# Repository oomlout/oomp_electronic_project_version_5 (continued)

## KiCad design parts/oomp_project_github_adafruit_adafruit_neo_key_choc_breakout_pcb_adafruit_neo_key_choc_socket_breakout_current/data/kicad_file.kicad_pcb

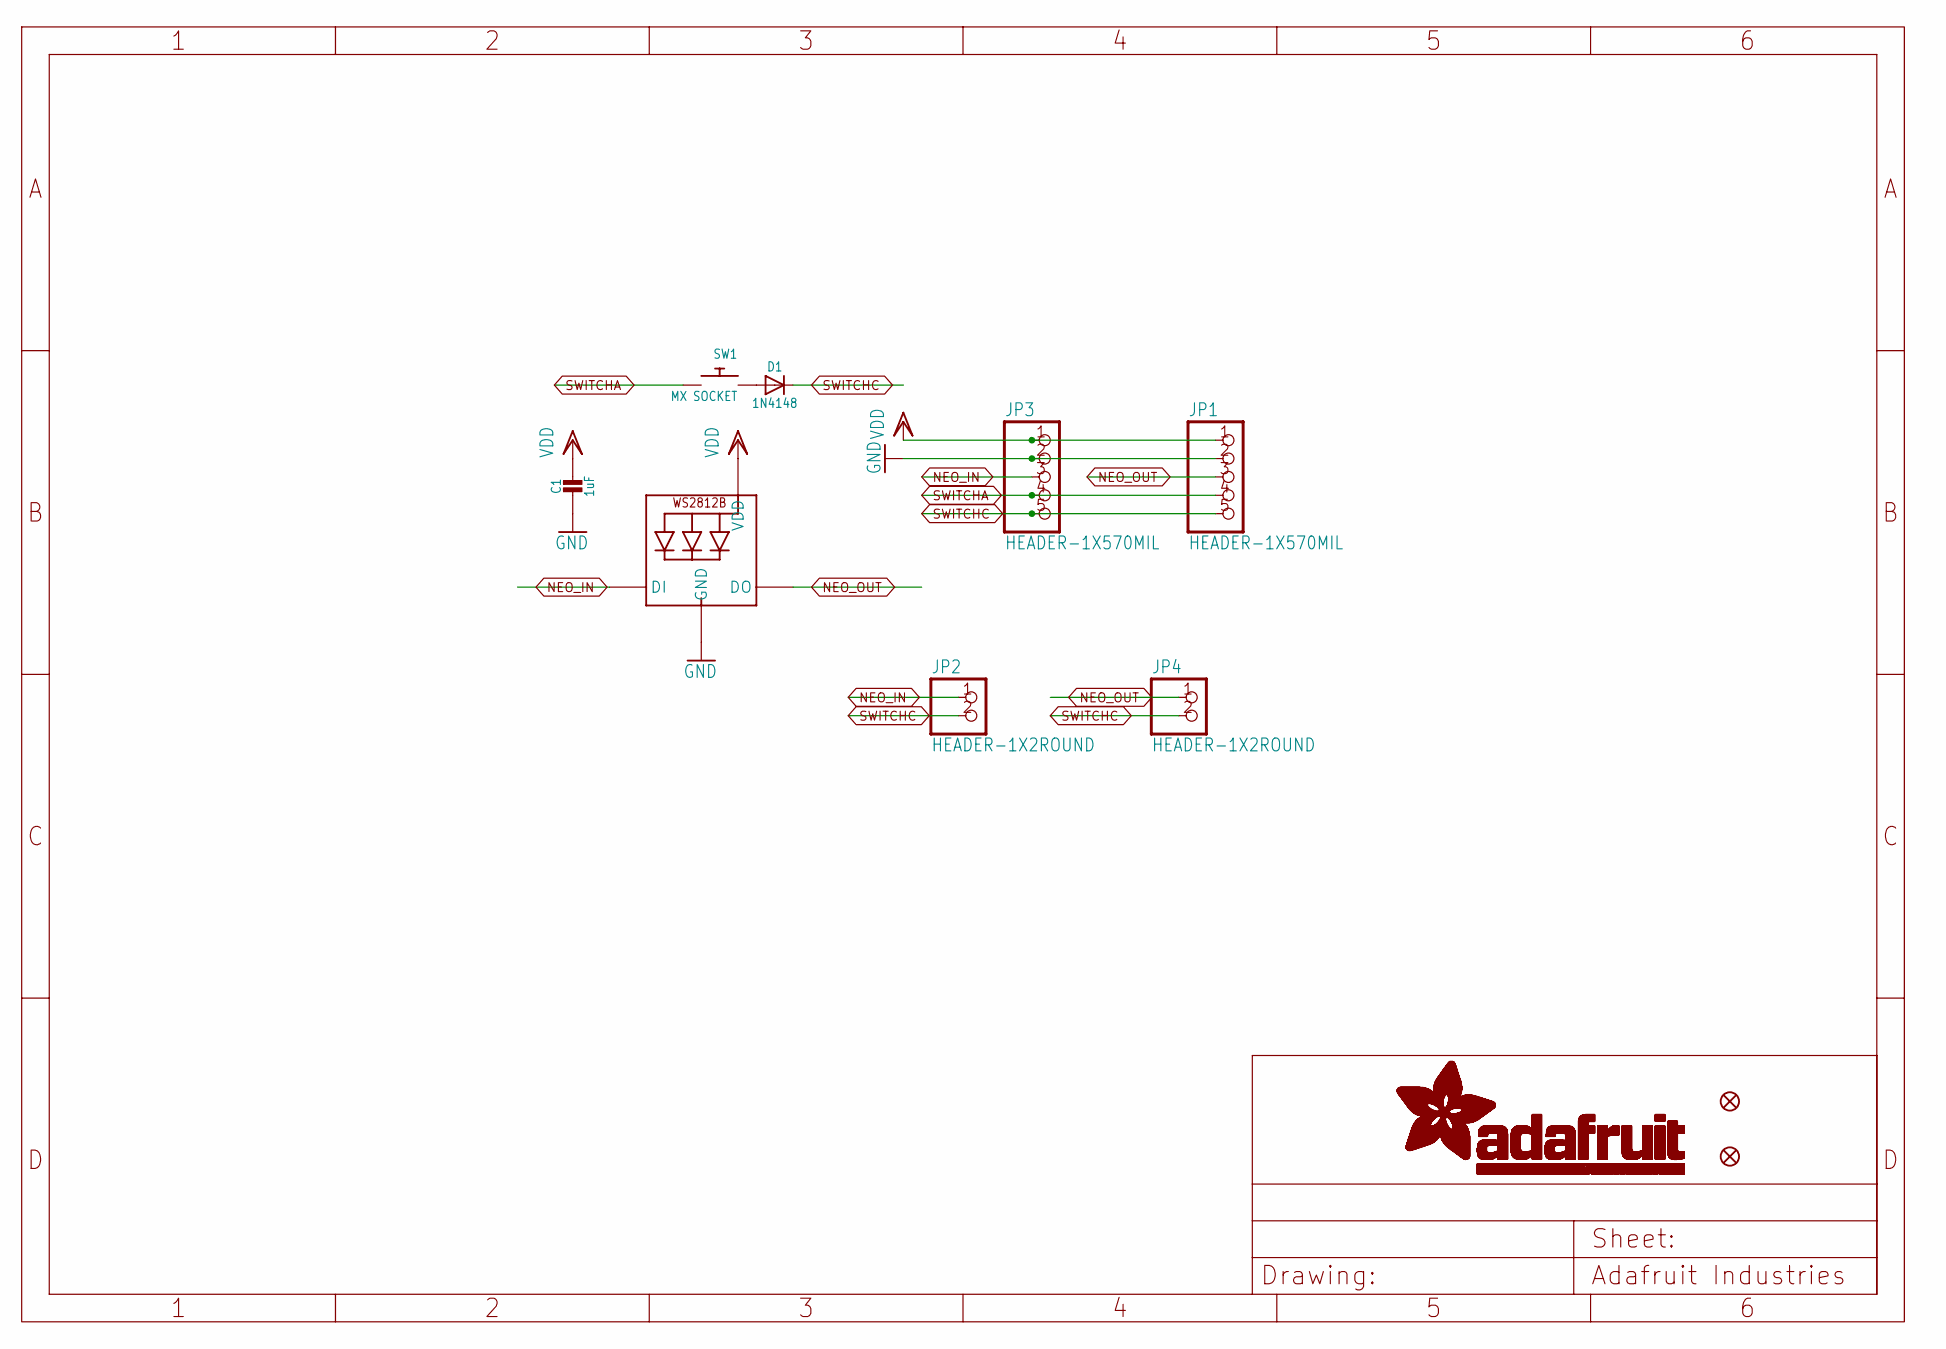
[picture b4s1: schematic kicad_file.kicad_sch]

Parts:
C1: 1uF; 0603-NO
D1: 1N4148; SOD-323
FID3, FID4: FIDUCIAL_1MM
JP1, JP3: HEADER-1X570MIL; 1X05_ROUND_70
JP2, JP4: HEADER-1X2ROUND; 1X02_ROUND
LED1: WS2812B_SK6812E; NEO3535_REVERSE
SW1: MX SOCKET; KAILH_CHOC_SOCKET

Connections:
GND: C1.2, JP1.2, JP3.2, LED1.3-GND (GND)
unnamed: D1.A, SW1.1
NEO_IN: JP2.1, JP3.3, LED1.4-DIN (DI)
NEO_OUT: JP1.3, JP4.1, LED1.2-DOUT (DO)
SWITCHA: JP1.4, JP3.4, SW1.2
SWITCHC: D1.C, JP1.5, JP2.2, JP3.5, JP4.2
VDD: C1.1, JP1.1, JP3.1, LED1.1-VDD (VDD)

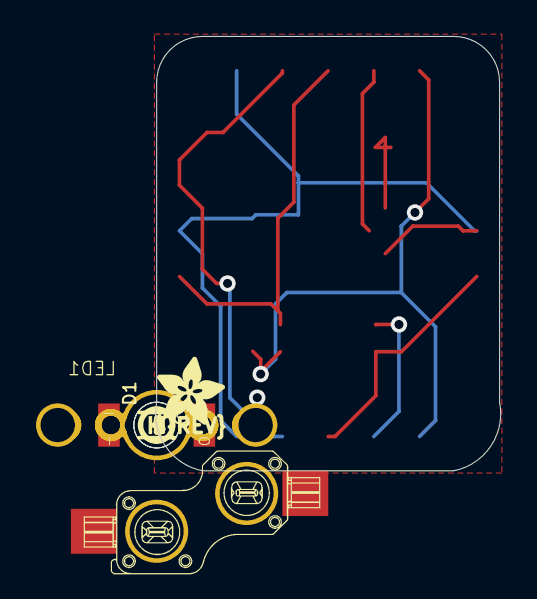
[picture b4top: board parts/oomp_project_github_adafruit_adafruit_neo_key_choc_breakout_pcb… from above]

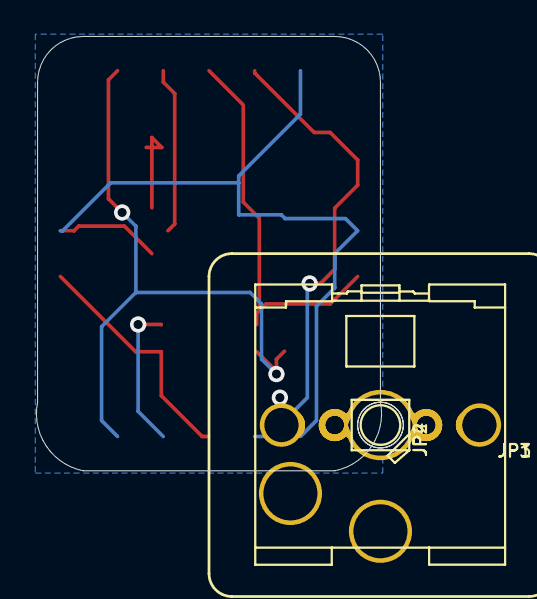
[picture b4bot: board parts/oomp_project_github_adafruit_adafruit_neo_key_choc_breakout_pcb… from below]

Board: 2 copper layers, 19.2 x 24.1 mm, 39 parts (16 on the bottom side), 7 nets.

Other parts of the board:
PLABEL0, PLABEL20: PLABEL0
PLABEL1: PLABEL1
PLABEL2: PLABEL2
PLABEL3: PLABEL3
PLABEL4: PLABEL4
PLABEL5: PLABEL5
PLABEL6, PLABEL21: PLABEL6
PLABEL7: PLABEL7
PLABEL8, PLABEL22: PLABEL8
PLABEL9, PLABEL23: PLABEL9
PLABEL10: PLABEL10
PLABEL11: PLABEL11
PLABEL12: PLABEL12
PLABEL13: PLABEL13
PLABEL14: PLABEL14
PLABEL15: PLABEL15
PLABEL16: PLABEL16
PLABEL17: PLABEL17
PLABEL18: PLABEL18
PLABEL19: PLABEL19
PLABEL200: PLABEL200
U$1: PCBFEAT-REV-040
U$2: ADAFRUIT_3.5MM
UNK_HOLE_0: dummyfp0
UNK_HOLE_1: dummyfp1

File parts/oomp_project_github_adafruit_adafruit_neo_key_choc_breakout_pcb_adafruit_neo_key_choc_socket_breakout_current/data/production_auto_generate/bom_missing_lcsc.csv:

Designator,Comment,Footprint,OOMP ID,Reason
D1,1N4148,Adafruit NeoKey CHOC Socket Breakout-import-fps:SOD-323,electronic_diode_switching_sod_323_onsemi_1n4148ws,No verified LCSC part number
LED1,WS2812B_SK6812E,Adafruit NeoKey CHOC Socket Breakout-import-fps:NEO3535_REVERSE,,No verified LCSC part number
PLABEL0,,Adafruit NeoKey CHOC Socket Breakout-import-fps:PLABEL0,,No verified LCSC part number
PLABEL1,,Adafruit NeoKey CHOC Socket Breakout-import-fps:PLABEL1,,No verified LCSC part number
PLABEL2,,Adafruit NeoKey CHOC Socket Breakout-import-fps:PLABEL2,,No verified LCSC part number
PLABEL3,,Adafruit NeoKey CHOC Socket Breakout-import-fps:PLABEL3,,No verified LCSC part number
PLABEL4,,Adafruit NeoKey CHOC Socket Breakout-import-fps:PLABEL4,,No verified LCSC part number
PLABEL5,,Adafruit NeoKey CHOC Socket Breakout-import-fps:PLABEL5,,No verified LCSC part number
PLABEL6,,Adafruit NeoKey CHOC Socket Breakout-import-fps:PLABEL6,,No verified LCSC part number
PLABEL7,,Adafruit NeoKey CHOC Socket Breakout-import-fps:PLABEL7,,No verified LCSC part number
PLABEL8,,Adafruit NeoKey CHOC Socket Breakout-import-fps:PLABEL8,,No verified LCSC part number
PLABEL9,,Adafruit NeoKey CHOC Socket Breakout-import-fps:PLABEL9,,No verified LCSC part number
PLABEL10,,Adafruit NeoKey CHOC Socket Breakout-import-fps:PLABEL10,,No verified LCSC part number
PLABEL11,,Adafruit NeoKey CHOC Socket Breakout-import-fps:PLABEL11,,No verified LCSC part number
PLABEL12,,Adafruit NeoKey CHOC Socket Breakout-import-fps:PLABEL12,,No verified LCSC part number
PLABEL13,,Adafruit NeoKey CHOC Socket Breakout-import-fps:PLABEL13,,No verified LCSC part number
PLABEL14,,Adafruit NeoKey CHOC Socket Breakout-import-fps:PLABEL14,,No verified LCSC part number
PLABEL15,,Adafruit NeoKey CHOC Socket Breakout-import-fps:PLABEL15,,No verified LCSC part number
PLABEL16,,Adafruit NeoKey CHOC Socket Breakout-import-fps:PLABEL16,,No verified LCSC part number
PLABEL17,,Adafruit NeoKey CHOC Socket Breakout-import-fps:PLABEL17,,No verified LCSC part number
PLABEL18,,Adafruit NeoKey CHOC Socket Breakout-import-fps:PLABEL18,,No verified LCSC part number
PLABEL19,,Adafruit NeoKey CHOC Socket Breakout-import-fps:PLABEL19,,No verified LCSC part number
PLABEL20,,Adafruit NeoKey CHOC Socket Breakout-import-fps:PLABEL0,,No verified LCSC part number
PLABEL21,,Adafruit NeoKey CHOC Socket Breakout-import-fps:PLABEL6,,No verified LCSC part number
PLABEL22,,Adafruit NeoKey CHOC Socket Breakout-import-fps:PLABEL8,,No verified LCSC part number
PLABEL23,,Adafruit NeoKey CHOC Socket Breakout-import-fps:PLABEL9,,No verified LCSC part number
PLABEL200,,Adafruit NeoKey CHOC Socket Breakout-import-fps:PLABEL200,,No verified LCSC part number
SW1,MX SOCKET,Adafruit NeoKey CHOC Socket Breakout-import-fps:KAILH_CHOC_SOCKET,,No verified LCSC part number
U$1,,Adafruit NeoKey CHOC Socket Breakout-import-fps:PCBFEAT-REV-040,,No verified LCSC part number
U$2,,Adafruit NeoKey CHOC Socket Breakout-import-fps:ADAFRUIT_3.5MM,,No verified LCSC part number
